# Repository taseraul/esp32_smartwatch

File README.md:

# esp32_smartwatch

Work in progress for a ESP32 smartwatch

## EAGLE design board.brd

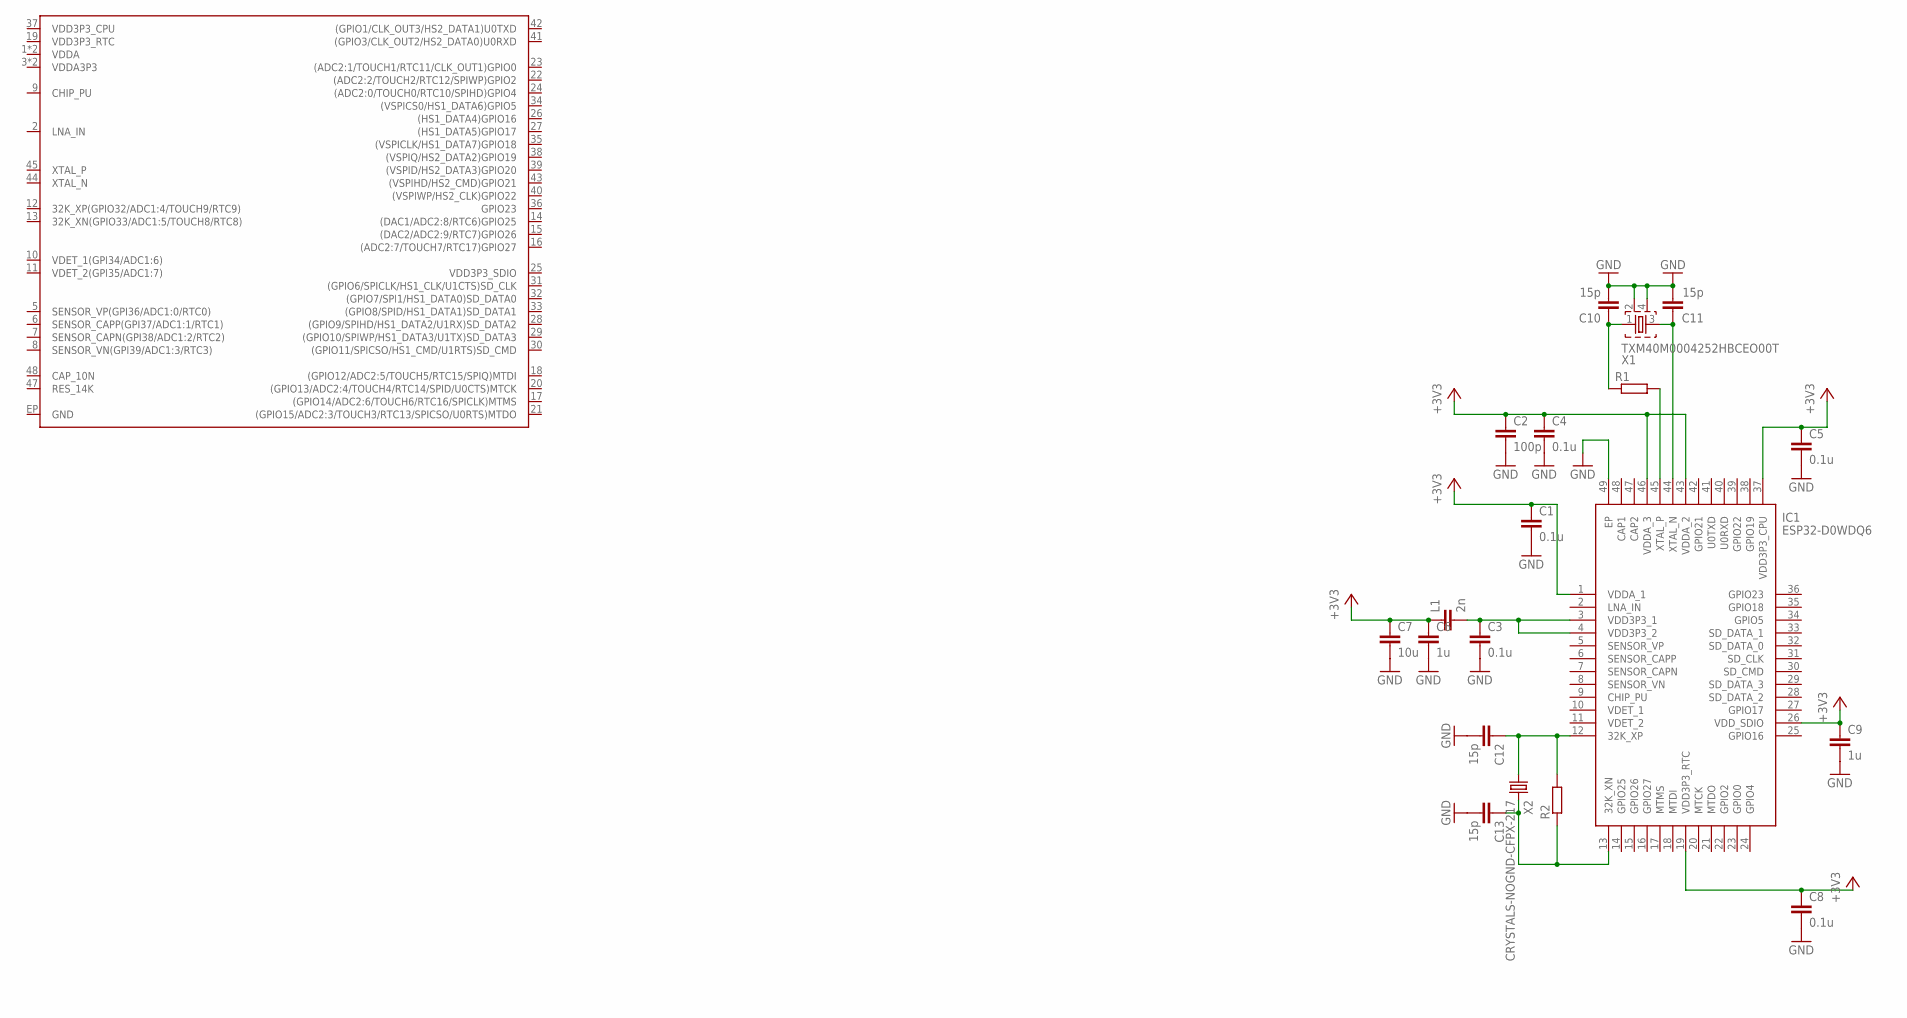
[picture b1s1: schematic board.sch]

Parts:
C1, C3, C4, C5, C8: 0.1u; C0402
C2: 100p; C0402
C6, C9: 1u; C0402
C7: 10u; C0603
C10, C11, C12, C13: 15p; C0402
IC1: ESP32-D0WDQ6; QFN40P600X600X90-49N
L1: 2n; C0402K
R1, R2: R-EU_R0402; R0402
U$1: ESP32; QFN48-0.4MM
X1: TXM40M0004252HBCEO00T; 2.5X2-4-PAD
X2: CRYSTALS-NOGND-CFPX-217; 3.2X1.5-2-PAD

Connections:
+3V3: C1.1, C2.1, C4.1, C5.1, C6.1, C7.1, C8.1, C9.1, IC1.1 (VDDA_1), IC1.19 (VDD3P3_RTC), IC1.26 (VDD_SDIO), IC1.37 (VDD3P3_CPU), IC1.43 (VDDA_2), IC1.46 (VDDA_3), L1.1
GND: C1.2, C2.2, C3.2, C4.2, C5.2, C6.2, C7.2, C8.2, C9.2, C10.2, C11.2, C12.2, C13.2, IC1.49 (EP), X1.2, X1.4
unnamed: C10.1, R1.1, X1.1
unnamed: C3.1, IC1.3 (VDD3P3_1), IC1.4 (VDD3P3_2), L1.2
unnamed: C11.1, IC1.44 (XTAL_N), X1.3
unnamed: IC1.45 (XTAL_P), R1.2
unnamed: C12.1, IC1.12 (32K_XP), R2.2, X2.1
unnamed: C13.1, IC1.13 (32K_XN), R2.1, X2.2

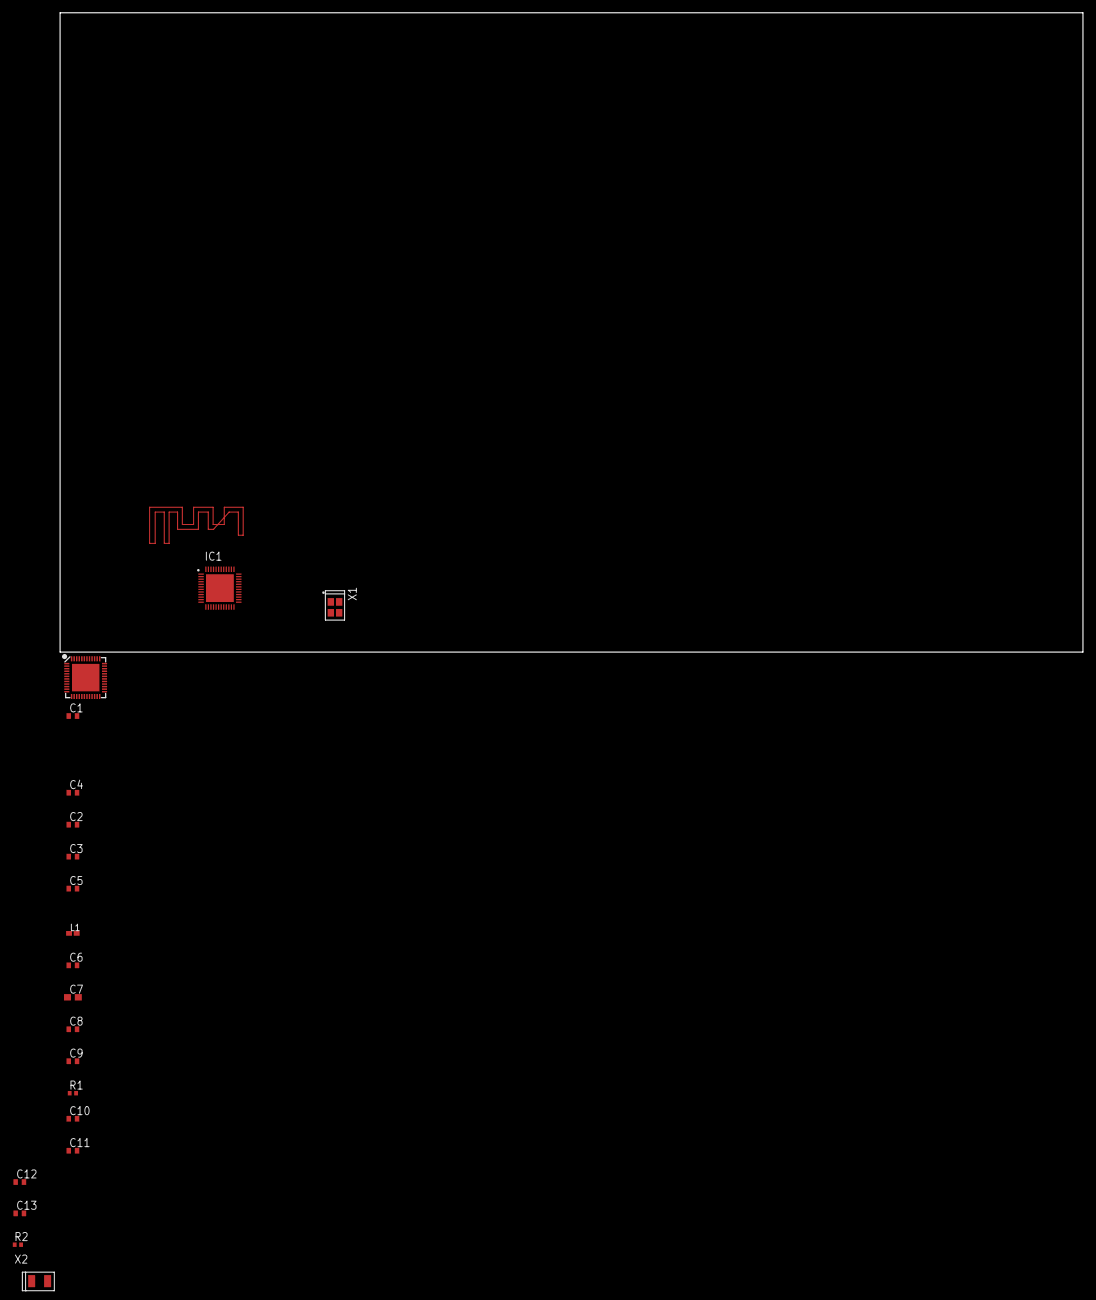
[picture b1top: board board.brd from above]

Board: 4 copper layers, 160.0 x 100.0 mm, 20 parts (0 on the bottom side), 8 nets.

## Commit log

2020-07-03 ESP power management v1
